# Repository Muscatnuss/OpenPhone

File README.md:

# Open Phone

# ToDo
- [ ] Accessories
	- [ ] Flashlight
- [ ] Human Interface
	- [ ] Vibration
	- [ ] Speaker
	- [ ] Fingerprint Sensor
- [ ] Connectivity
	- [x] Data - USB-C
		- [x] (SBUS Data)
	- [ ] (LORA communication)
		- meshtastic
	- [x] Cellular
- [ ] Sensors
	- [x] IMU
	- [x] Magnetometer
	- [ ] Fingerprint
- [ ] Video
	- [ ] Display
	- [ ] Camera
	- [ ] HDMI
- [ ] Audio
	- [ ] cellular audio $\to$ USB
	- [ ] CM5 audio IO
- [ ] Power
	- [ ] Load Switch 
		- [x] Modem
		- [ ] Camera
		- [ ] Mic
	- [x] USB-C Power delivery
	- [x] Power usage monitoring
		- [x] Current Monitor
		- [x] Voltage Monitor
# Hardware
- Back of PCB should face the screen
	- only very flat components on back
- PCB cutout for battery
    - Battery and PCB are on the same height to save space 

## Thermal management
- all significant heat producers face back
- Battery and screen keep a distance to hot spots

## Controller
Raspberry pi compute Module
https://www.raspberrypi.com/documentation/computers/compute-module.html#compute-module-5
https://datasheets.raspberrypi.com/cm5/cm5-datasheet.pdf
$\to$ 5V supply
$\to$ [Board connector](https://www.mouser.de/ProductDetail/Amphenol-FCI/10164227-1001A1RLF?qs=MyNHzdoqoQIc%2Fqhi8q%2FTOw%3D%3D)
Normalbetrieb unter Last $\to$ ~500mA

## Speicher
### SD Karte
- over SPI

## Screen
IPhone Xr 460ppi  ~6 Zoll

|                                                                                                                                                                         | size  | maße                         | resolution  | price | Flex | Händler |
| ----------------------------------------------------------------------------------------------------------------------------------------------------------------------- | ----- | ---------------------------- | ----------- | ----- | ---- | ------- |
| [FLEX](https://www.alibaba.com/product-detail/Super-Thin-6-67-inch-1080_1601047701892.html?spm=a2700.galleryofferlist.normal_offer.d_title.4c7013a07lG6Xn)              | 6,67" | 165,16mm x 71,532mm x 0,33mm | 1080 x 2160 | 95€   | ja   | Alibaba |
| [6" Flex](https://www.alibaba.com/product-detail/360-Degree-Bendable-6-Inch-Flexible_1600485553315.html?spm=a2700.galleryofferlist.normal_offer.d_title.4c7013a07lG6Xn) | 6"    | 68.04 x 136,08mm             | 1080 x 2160 | 95€   | ja   | Alibaba |

## Connectivity

- WLan $\to$ schon da
- Bluetooth $\to$  schon da
- micro HDMI $\to$ just add connector
- Ethernet?
- Phone network
- NFC
- USB-C
	- device mode
	- host mode
		- USB-Sticks und so
- Headphone-jack

### 3G 4G 5G

| Link                                        | Price |         |                                                                | Manual                                              |
| ------------------------------------------- | ----- | ------- | -------------------------------------------------------------- | --------------------------------------------------- |
| https://mc-technologies.com/produkt/162368/ | 70€   |         |                                                                |                                                     |
| SIM7600G-H                                  | ~40€  | mit GPS | Dev-Board müsste man nachbauen, sollte aber nicht so wild sein | https://fcc.report/FCC-ID/2AJYU-8PYA007/4857209.pdf |
|                                             |       |         |                                                                |                                                     |

[NAU8810](https://octopart.com/de/datasheet/nau8810yg-nuvoton-29622521 ) $\to$ Audio Codec
[Microphone](https://octopart.com/de/ics-40618-invensense-71346755)

## Powersupply
$\to$ 5V Akku Ladeelektronik
[load switch](https://www.ti.com/lit/ds/symlink/tps22917.pdf?ts=1749349462384)

### Battery Controller
Charge and boost controller, Power Path Management
availlable JLC
[BQ25895](https://www.ti.com/lit/ds/symlink/bq25895.pdf) ~3€

### Battery

| Kapazität                                                                                                                                               | Maße           | Preis | Händler |
| ------------------------------------------------------------------------------------------------------------------------------------------------------- | -------------- | ----- | ------- |
| [5000mAh](https://www.alibaba.com/product-detail/Lithium-Polymer-ultra-Thin-Lipo-3_1868172466.html?spm=a2700.details.you_may_like.3.b10c349ePAwK8i)     | 6 x 50 x 82    | 3,80€ | Alibaba |
| [5500mAh](https://www.alibaba.com/product-detail/3-7-V-407595-5500mah-Factory_62168748778.html?spm=a2700.details.you_may_like.15.6f191303vtdQ68)        | 4 x 75 x 95mm  | 6,39€ | Alibaba |
| [10000mAh](https://www.alibaba.com/product-detail/8065113-3-7V-Lipo-Battery-10000mah_62109571526.html?spm=a2700.details.you_may_like.21.6f191303vtdQ68) | 8 x 65 x 113mm | 8,50€ | Alibaba |

## Sensors

- [[Inertial Measurement Unit|IMU]]
- 3D [[Magnetometer]]
- Fingerprint sensor
	- https://biometrics.mainguet.org/types/fingerprint/product/FPC/FPC_1020_flyer.pdf
		- SPI
- Camera

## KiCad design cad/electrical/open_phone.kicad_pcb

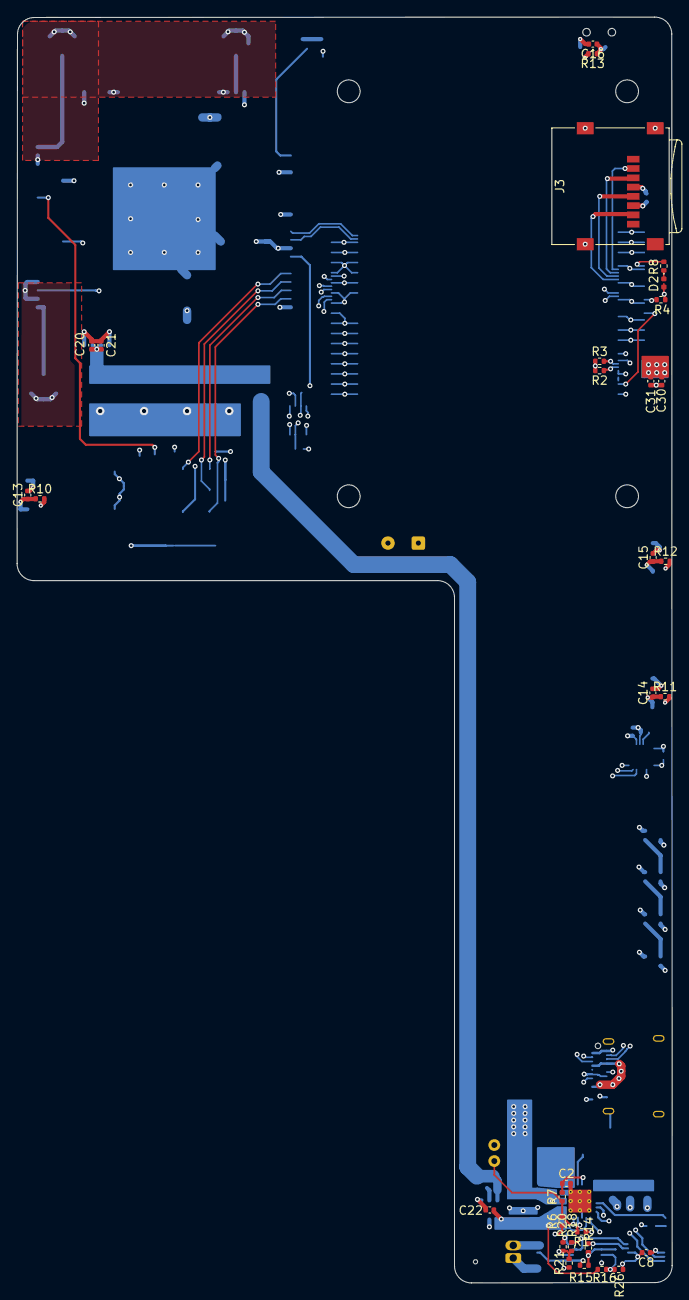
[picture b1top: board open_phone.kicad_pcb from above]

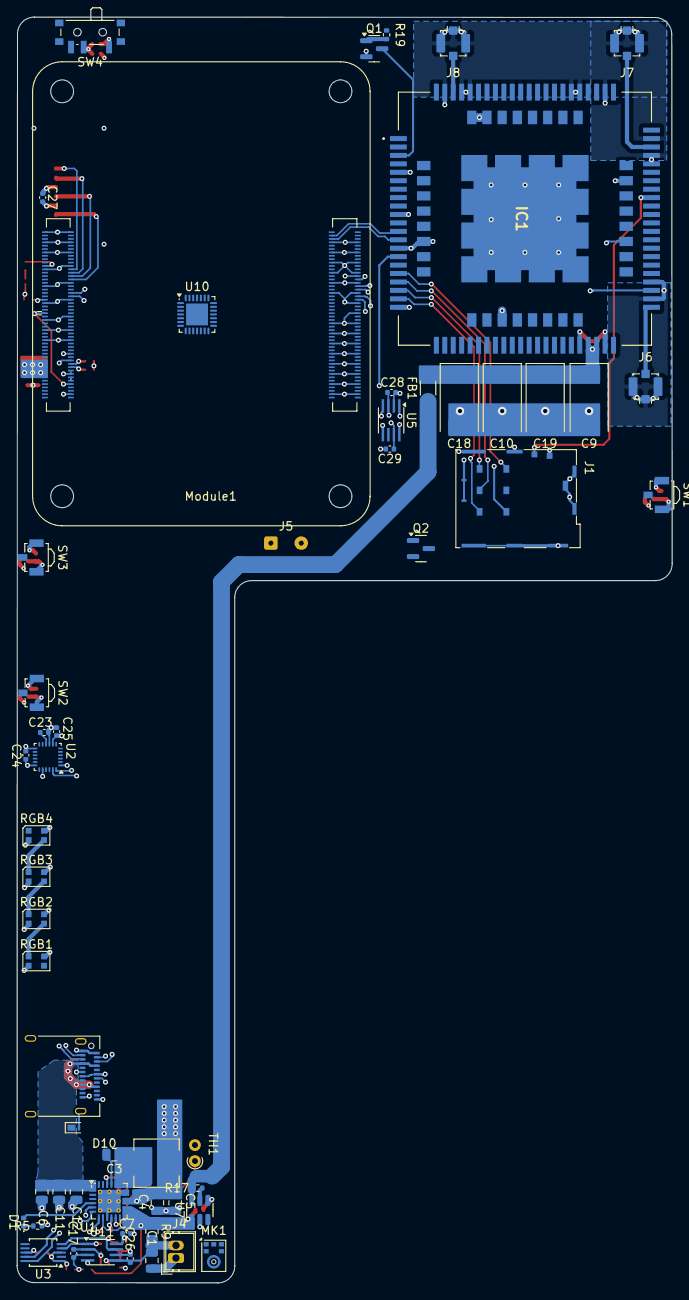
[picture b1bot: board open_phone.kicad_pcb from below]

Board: 6 copper layers, 77.6 x 150.0 mm, 87 parts (56 on the bottom side), 70 nets.

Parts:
C1, C3, C4, C5, C6, C11, C12: C; C_0805_2012Metric
C2, C7, C8, C13, C14, C15, C16, C17, C26, C27, C28, C29: C; C_0402_1005Metric
C9, C10, C18, C19: 100µF; CP_EIA-7343-31_Kemet-D
C20, C21, C22, C23, C24, C25, C30, C31: 100nF; C_0402_1005Metric
D1, D2: LED; LED_0402_1005Metric
D10: 12V; Nexperia_DSN1608-2_1.6x0.8mm
FB1: FerriteBead; L_1206_3216Metric
IC1: SIM7600G-H; SIM7600GH
J1: JAE_SIM_Card_SF72S006
J2: USB_C_Receptacle; USB_C_Receptacle_Amphenol_12401610E4-2A
J3: Micro_SD_Card; microSD_HC_Wuerth_693072010801
J4: Battery; Wuerth_WR-WTB_64800211622_1x02_P1.50mm_Vertical
J5: VIB; SolderWire-0.1sqmm_1x02_P3.6mm_D0.4mm_OD1mm
J6, J7, J8: conn_coax; U.FL_Molex_MCRF_73412-0110_Vertical
L1: L; L_Changjiang_FXL0518
MK1: ICS-43434; InvenSense_ICS-43434-6_3.5x2.65mm
Module1: ComputeModule5-CM5; Raspberry-Pi-5-Compute-Module
Q1, Q2: BC848; SOT-23
R1, R2, R3, R4, R5, R6, R7, R8, R10, R11, R12, R13, R14, R15, R16, R17, R18, R19, R20, R21, R26: R; R_0402_1005Metric
R9: R; R_0805_2012Metric
RGB1, RGB2, RGB3, RGB4: WS2812B-2020; LED_WS2812B-2020_PLCC4_2.0x2.0mm
SW1, SW2, SW3: SW_Push; SW_SPST_B3U-3100P
SW4: SW_SPST; SW_SPDT_PCM12
TH1: Thermistor_NTC; R_Axial_DIN0204_L3.6mm_D1.6mm_P1.90mm_Vertical
U1: BQ25895RTW; Texas_RTW_WQFN-24-1EP_4x4mm_P0.5mm_EP2.7x2.7mm_ThermalVias
U2: MPU-9250; InvenSense_QFN-24_3x3mm_P0.4mm
U3: ADS1013IDGS; TSSOP-10_3x3mm_P0.5mm
U5: TXS0102DCT; SSOP-8_2.95x2.8mm_P0.65mm
U7: TPS22917DBV; SOT-23-6
U10: ES8388; QFN-28-1EP_4x4mm_P0.45mm_EP2.6x2.6mm
U11: OPA2197xDGK; SSOP-8_2.95x2.8mm_P0.65mm

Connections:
+1V8: Module1.88 (+1.8v_(Output)), Module1.90 (+1.8v_(Output))
+1V8_CELL: C29.1, IC1.15 (VDD_1V8), U5.7 (VCCB)
+3.3V: C24.1, C25.1, C27.1, C28.2, D2.2 (A), J3.4 (VDD), J5.1, Module1.78 (GPIO_VREF(1.8v/3.3v_Input)), Module1.84 (+3.3v_(Output)), Module1.86 (+3.3v_(Output)), R2.2, R3.2, R4.2, RGB1.4 (VDD), RGB2.4 (VDD), RGB3.4 (VDD), RGB4.4 (VDD), U2.8 (VDDIO), U2.13 (VDD), U5.3 (VCCA)
+3V3: R10.2, R11.2, R12.2, R13.2, U2.1 (RESV_VDDIO)
+5V: C4.1, C5.1, C7.1, C8.1, C30.1, C31.1, L1.2, Module1.77 (+5v_(Input)), Module1.79 (+5v_(Input)), Module1.81 (+5v_(Input)), Module1.83 (+5v_(Input)), Module1.85 (+5v_(Input)), Module1.87 (+5v_(Input)), R5.1, R20.2, U1.15 (SYS), U1.16 (SYS), U3.8 (VDD), U11.8 (V+)
/cellular/MODEM_DBG_RX: IC1.106 (DBG_RXD), U5.8 (B1)
/cellular/MODEM_DBG_TX: IC1.42 (DBG_TXD), U5.1 (B2)
/cellular/MODEM_POWER: FB1.1, R17.1, U7.6 (VOUT)
/cellular/SW_MODEM: Module1.39 (GPIO8), U7.3 (ON)
/cellular/USB2_N: IC1.12 (USB_DN), Module1.103 (USB2_N)
/cellular/USB2_P: IC1.13 (USB_DP), Module1.105 (USB2_P)
/connectors/CC1: J2.A5 (CC1), Module1.94 (CC1)
/connectors/CC2: J2.B5 (CC2), Module1.96 (CC2)
/connectors/USB3-0-DN: J2.A7 (D-), J2.B7 (D-), Module1.134 (USB3-0-D_P)
/connectors/USB3-0-DP: J2.A6 (D+), J2.B6 (D+), Module1.136 (USB3-0-D_N)
/connectors/USB3-0-RX_N: J2.B10 (RX1-), Module1.130 (USB3-0-RX_P)
/connectors/USB3-0-RX_P: J2.B11 (RX1+), Module1.128 (USB3-0-RX_N)
/connectors/USB3-0-TX_N: J2.A3 (TX1-), Module1.142 (USB3-0-TX_P)
/connectors/USB3-0-TX_P: J2.A2 (TX1+), Module1.140 (USB3-0-TX_N)
/controller/CS: J3.2 (DAT3/CD), Module1.24 (GPIO26)
/controller/GPIO25: Module1.41 (GPIO25), R4.1, U1.7 (INT)
/controller/MISO: J3.3 (CMD), Module1.26 (GPIO19)
/controller/MOSI: J3.7 (DAT0), Module1.30 (GPIO6)
/controller/SCL0: Module1.80 (SCL0), R3.1, U1.5 (SCL), U2.23 (SCL/SCLK), U3.10 (SCL)
/controller/SCLK: J3.5 (CLK), Module1.28 (GPIO13)
/controller/SDA0: Module1.82 (SDA0), R2.1, U1.6 (SDA), U2.24 (SDA/MOSI), U3.9 (SDA)
/controller/UART0_RX: Module1.40 (GPIO9), U5.5 (A1)
/controller/UART0_TX: Module1.38 (GPIO11), U5.4 (A2)
BTTN_VOL_+: C14.1, R11.1, SW2.2
BTTN_VOL_-: C15.1, R12.1, SW3.2
BTTN_unlock: C13.1, Module1.49 (GPIO18), Module1.92 (PWR_BUT), R10.1, SW1.2
GND: C1.2, C2.2, C4.2, C5.2, C6.1, C7.2, C8.2, C9.2, C10.2, C11.1, C12.1, C13.2, C14.2, C15.2, C16.2, C18.2, C19.2, C20.2, C21.2, C23.2, C24.2, C25.2, C27.2, C28.1, C29.2, C30.2, C31.2, D10.2 (A), IC1.1 (GND_1), IC1.2 (GND_2), IC1.5 (GND_3), IC1.10 (GND_4), IC1.14 (GND_5), IC1.37 (GND_6), IC1.40 (GND_7), IC1.41 (GND_8), IC1.43 (GND_9), IC1.57 (GND_10), IC1.58 (GND_11), IC1.60 (GND_12), IC1.61 (GND_13), IC1.64 (GND_14), IC1.65 (GND_15), IC1.77 (GND_16), IC1.78 (GND_17), IC1.80 (GND_18), IC1.81 (GND_19), IC1.93 (GND_20), IC1.98 (GND_21), IC1.110 (GND_22), IC1.118 (GND_23), IC1.119 (GPIO_19), IC1.120 (GND_24), IC1.121 (GND_25), IC1.122 (GND_26), IC1.123 (GND_27), IC1.124 (GND_28), IC1.125 (GND_29), IC1.126 (GND_30), IC1.127 (GND_31), IC1.128 (GND_32), IC1.129 (GND_33), IC1.130 (GND_34), IC1.131 (GND_35), IC1.132 (GND_36), IC1.133 (GND_37), IC1.134 (GND_38), IC1.135 (GND_39), J1.C5 (GND), J1.DSW, J1.SH, J2.A1 (GND), J2.A12 (GND), J2.B1 (GND), J2.B12 (GND), J2.S1 (SHIELD), J3.6 (VSS), J3.9 (SHIELD), J4.1, J6.2 (Ext), J7.2 (Ext), J8.2 (Ext), Module1.1 (GND), Module1.2 (GND), Module1.7 (GND), Module1.8 (GND), Module1.13 (GND), Module1.14 (GND), Module1.22 (GND), Module1.23 (GND), Module1.32 (GND), Module1.33 (GND), Module1.42 (GND), Module1.43 (GND), Module1.52 (GND), Module1.53 (GND), Module1.59 (GND), Module1.60 (GND), Module1.65 (GND), Module1.66 (GND), Module1.74 (GND), Module1.98 (GND), Module1.107 (GND), Module1.108 (GND), Module1.113 (GND), Module1.114 (GND), Module1.119 (GND), Module1.120 (GND), Module1.125 (GND), Module1.126 (GND), Module1.131 (GND), Module1.132 (GND), Module1.137 (GND), Module1.138 (GND), Module1.144 (GND), Module1.150 (GND), Module1.155 (GND), Module1.156 (GND), Module1.161 (GND), Module1.162 (GND), Module1.167 (GND), Module1.168 (GND), Module1.173 (GND), Module1.174 (GND), Module1.179 (GND), Module1.180 (GND), Module1.185 (GND), Module1.186 (GND), Module1.191 (GND), Module1.192 (GND), Module1.197 (GND), Module1.198 (GND), Q1.2 (E), Q2.2 (E), R1.1, R6.1, R21.1, R26.2, RGB1.2 (VSS), RGB2.2 (VSS), RGB3.2 (VSS), RGB4.2 (VSS), SW1.1, SW2.1, SW3.1, SW4.1 (A), TH1.2, U1.9 (~CE), U1.17 (PGND), U1.18 (PGND), U1.25 (PGND), U2.9 (AD0/MISO), U2.18 (GND), U2.20 (RESV_GND), U3.1 (ADDR), U3.3 (GND), U5.2 (GND), U7.2 (GND), U11.4 (V-)
LED_nACT: Module1.21 (LED_nACT), R8.1
unnamed: C3.1, L1.1, U1.19 (SW), U1.20 (SW)
unnamed: D1.2 (A), U1.4 (STAT)
unnamed: D1.1 (K), R5.2
unnamed: D2.1 (K), R8.2
unnamed: IC1.59 (AUX_ANT), J7.1 (In)
unnamed: IC1.79 (GNSS_ANT), J8.1 (In)
unnamed: IC1.82 (MAIN_ANT), J6.1 (In)
unnamed: IC1.3 (PWRKEY), Q1.3 (C)
unnamed: IC1.19 (USIM_CLK), J1.C3 (CLK)
unnamed: IC1.17 (USIM_DATA), J1.C7 (I/O)
unnamed: IC1.53 (USIM_DET~), J1.CSW
unnamed: IC1.18 (USIM_RST), J1.C2 (RST)
unnamed: IC1.20 (USIM_VDD), J1.C1 (VCC)
unnamed: C9.1, C10.1, C18.1, C19.1, C20.1, C21.1, FB1.2, IC1.38 (VBAT_1), IC1.39 (VBAT_2)
unnamed: C1.1, C26.2, J4.2, R9.2, R15.2, U11.5 (+)
unnamed: J5.2, Q2.3 (C)
unnamed: Module1.45 (GPIO24), Module1.91 (BT_nDisable)
unnamed: Module1.47 (GPIO23), Module1.89 (WiFi_nDisable)
unnamed: Q1.1 (B), R19.1
unnamed: RGB1.1 (DOUT), RGB2.3 (DIN)
unnamed: RGB2.1 (DOUT), RGB3.3 (DIN)
unnamed: RGB3.1 (DOUT), RGB4.3 (DIN)
unnamed: C3.2, U1.21 (BTST)
unnamed: R1.2, U1.10 (ILIM)
unnamed: C2.1, R7.2, U1.22 (REGN)
unnamed: R6.2, R7.1, TH1.1, U1.11 (TS)
unnamed: C23.1, U2.10 (REGOUT)
unnamed: R14.1, U3.4 (AIN0), U11.1
unnamed: R18.2, U3.5 (AIN1), U11.7
unnamed: C22.2, U7.4 (CT)
unnamed: R17.2, U7.5 (QOD)
unnamed: C17.1, R16.1, R26.1, U11.3 (+)
unnamed: C17.2, R14.2, R15.1, U11.2 (-)
unnamed: C26.1, R18.1, R20.1, R21.2, U11.6 (-)
SW_silent: C16.1, R13.1, SW4.2 (B)
VBUS_DP: C6.2, C11.2, C12.2, D10.1 (K), J2.A4 (VBUS), J2.A9 (VBUS), J2.B4 (VBUS), J2.B9 (VBUS), U1.1 (VBUS)
V_BAT: C22.1, R9.1, R16.2, U1.8 (OTG), U1.13 (BAT), U1.14 (BAT), U7.1 (VIN)

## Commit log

2025-08-09 backup
2025-08-09 translated stuff to english
